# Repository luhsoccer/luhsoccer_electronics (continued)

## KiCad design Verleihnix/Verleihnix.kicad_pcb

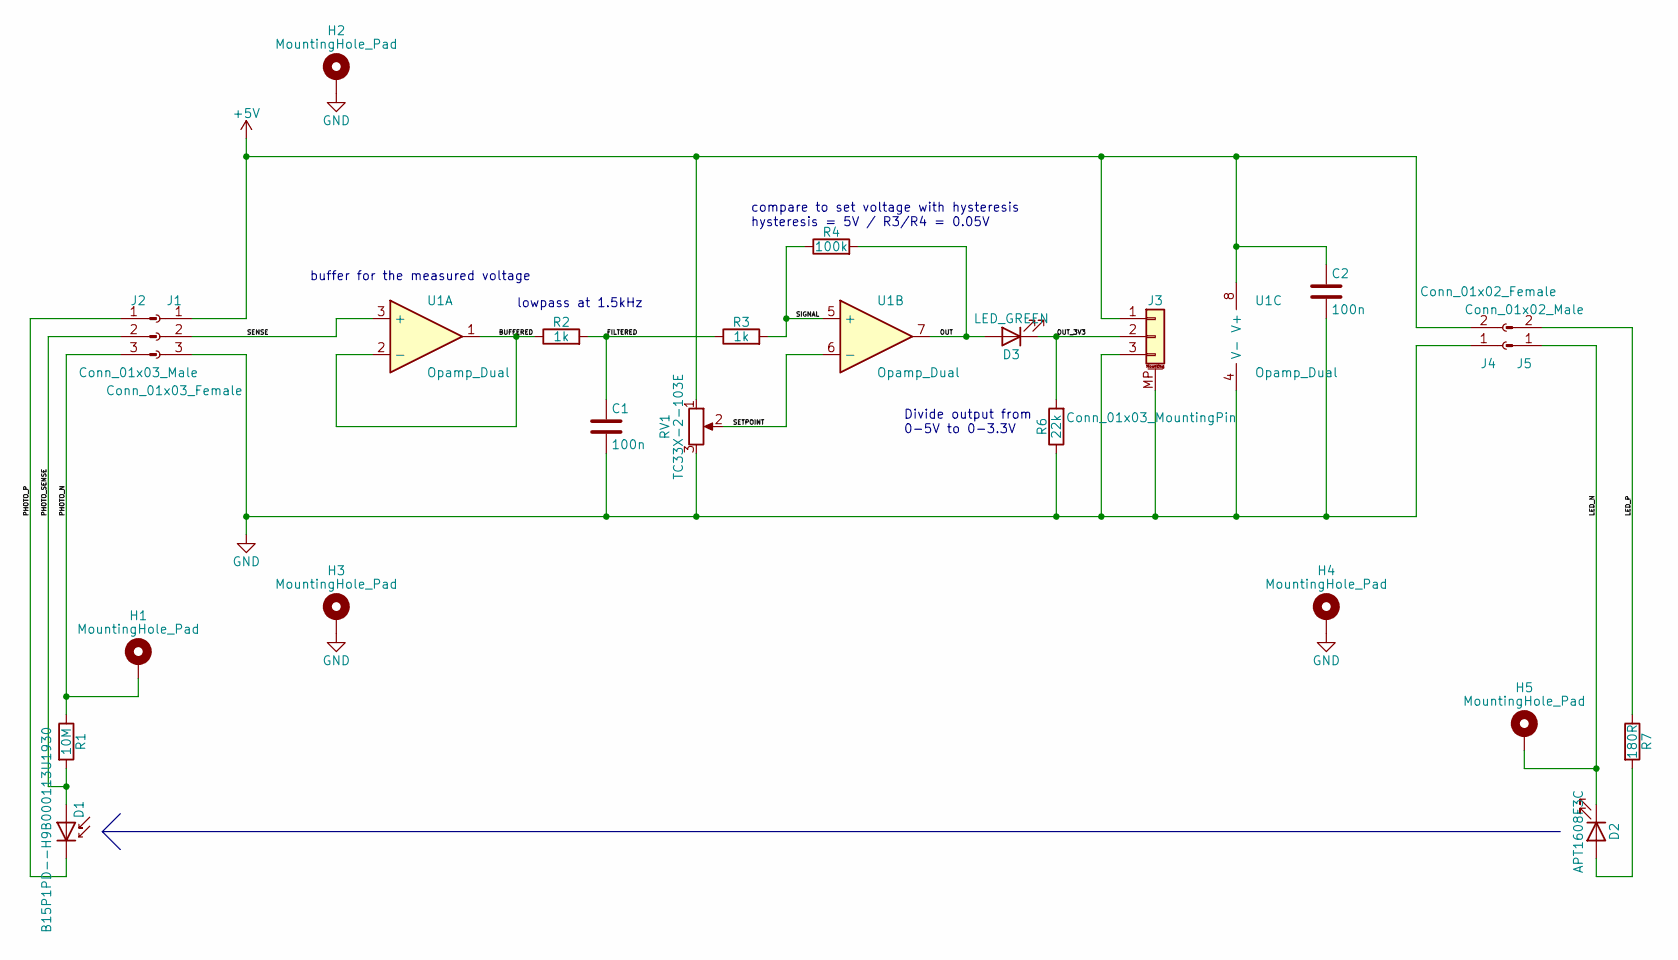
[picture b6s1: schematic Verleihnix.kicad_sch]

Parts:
C1, C2: 100n; C_0402_1005Metric
D1: B15P1PD--H9B000113U1930; LED_1210_3225Metric
D2: APT1608F3C; LED_0603_1608Metric
D3: LED_GREEN; LED_0603_1608Metric
H1, H2, H3, H4, H5: MountingHole_Pad; MountingHole_3.2mm_M3_DIN965_Pad
J1: Conn_01x03_Female; PinSocket_1x03_P2.54mm_Vertical
J2: Conn_01x03_Male; Pinheader_P2.54_01x03_Horizontal
J3: Conn_01x03_MountingPin; JST_PH_B3B-PH-SM4-TB_1x03-1MP_P2.00mm_Vertical
J4: Conn_01x02_Female; PinSocket_1x02_P2.54mm_Vertical
J5: Conn_01x02_Male; Pinheader_P2.54_01x02_Horizontal
R1: 10M; R_0402_1005Metric
R2, R3: 1k; R_0402_1005Metric
R4: 100k; R_0402_1005Metric
R6: 22k; R_0402_1005Metric
R7: 180R; R_0603_1608Metric
RV1: TC33X-2-103E; Potentiometer_Bourns_TC33X_Vertical
U1: Opamp_Dual; SOIC-8_3.9x4.9mm_P1.27mm

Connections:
+5V: C2.1, J1.1, J3.1, J4.2, RV1.1, U1.8 (V+)
/BUFFERED: R2.1, U1.1, U1.2 (-)
/FILTERED: C1.1, R2.2, R3.1
/LED_N: D2.1 (K), H5.1, J5.1
/LED_P: J5.2, R7.1
/OUT: D3.2 (A), R4.2, U1.7
/OUT_3V3: D3.1 (K), J3.2, R6.2
/PHOTO_N: H1.1, J2.3, R1.1
/PHOTO_P: D1.1 (K), J2.1
/PHOTO_SENSE: D1.2 (A), J2.2, R1.2
/SENSE: J1.2, U1.3 (+)
/SETPOINT: RV1.2, U1.6 (-)
/SIGNAL: R3.2, R4.1, U1.5 (+)
GND: C1.2, C2.2, H2.1, H3.1, H4.1, J1.3, J3.3, J3.MP (MountPin), J4.1, R6.1, RV1.3, U1.4 (V-)
unnamed: D2.2 (A), R7.2

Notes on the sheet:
compare to set voltage with hysteresis hysteresis = 5V / R3/R4 = 0.05V
buffer for the measured voltage
Divide output from 0-5V to 0-3.3V
lowpass at 1.5kHz

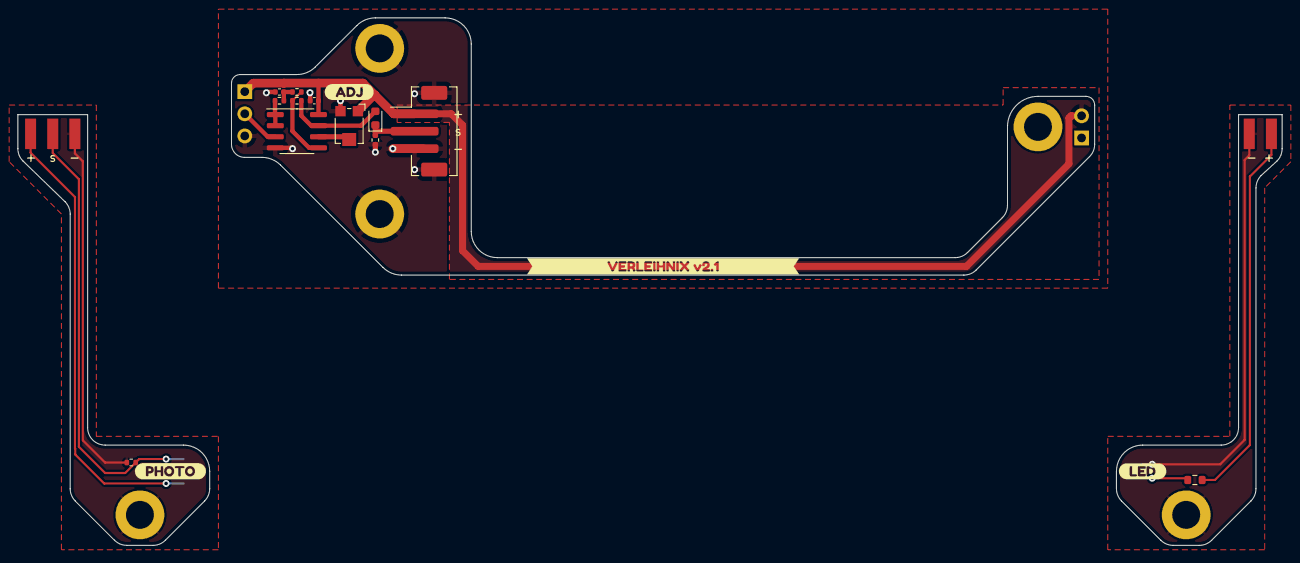
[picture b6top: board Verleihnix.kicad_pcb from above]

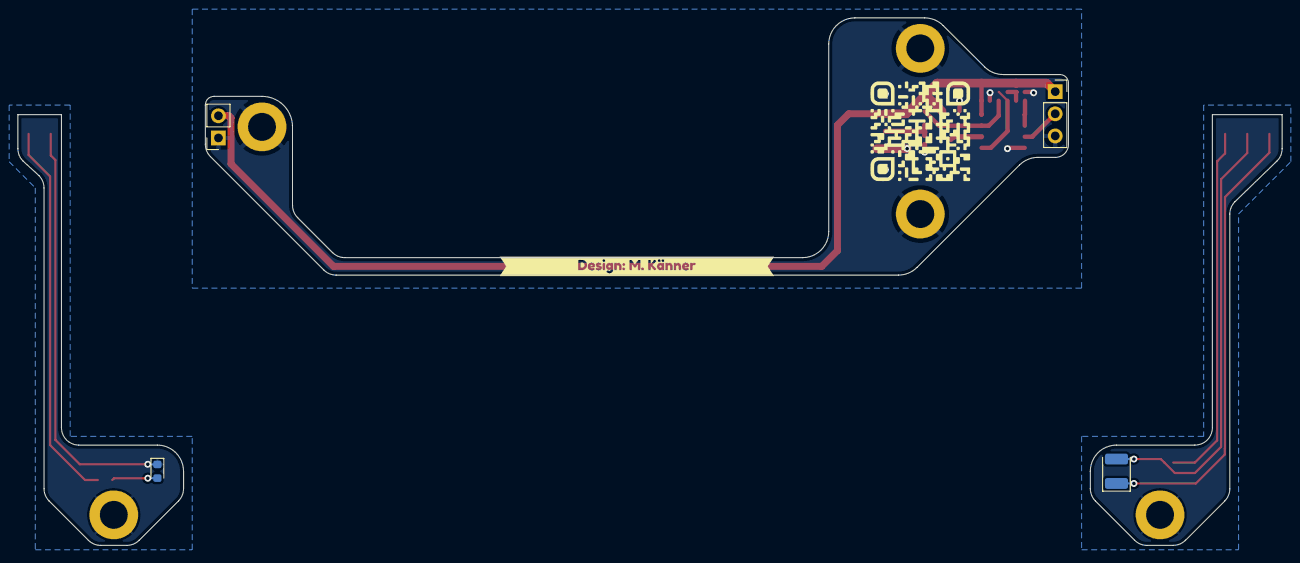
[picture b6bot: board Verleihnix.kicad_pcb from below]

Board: 2 copper layers, 145.0 x 60.5 mm, 28 parts (5 on the bottom side), 15 nets.

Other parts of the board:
kibuzzard-63F3637C: G***; kibuzzard-63F3637C
kibuzzard-635AD9F8: G***; kibuzzard-635AD9F8
kibuzzard-635AD93F: G***; kibuzzard-635AD93F
kibuzzard-635AD94A: G***; kibuzzard-635AD94A
kibuzzard-635AE38B: G***; kibuzzard-635AE38B

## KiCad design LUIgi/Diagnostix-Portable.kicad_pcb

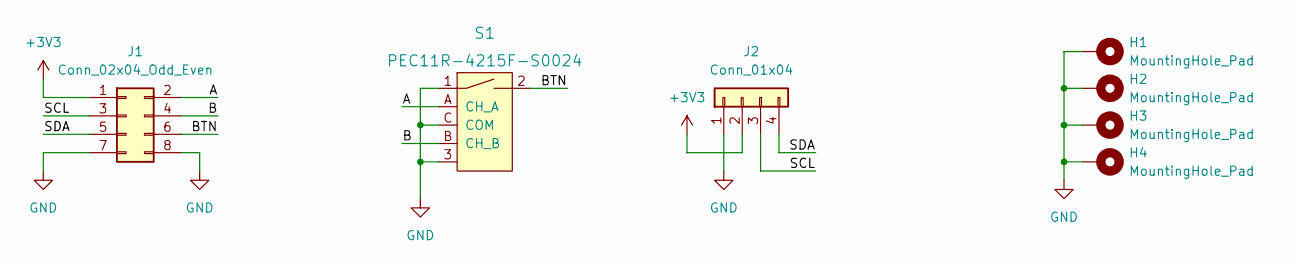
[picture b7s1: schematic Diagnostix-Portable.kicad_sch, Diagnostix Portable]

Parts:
H1, H2, H3, H4: MountingHole_Pad; MountingHole_3.2mm_M3_DIN965_Pad
J1: Conn_02x04_Odd_Even; IDC-Header_2x04_P2.54mm_Vertical
J2: Conn_01x04; PinSocket_1x04_P2.54mm_Vertical
S1: PEC11R-4215F-S0024; Rotary_Encoder_Switched_PEC11R; MPN PEC11R-4215F-S0024; Digi-Key_PN PEC11R-4215F-S0024-ND

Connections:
+3V3: J1.1, J2.2
/A: J1.2, S1.A (CH_A)
/B: J1.4, S1.B (CH_B)
/BTN: J1.6, S1.2
/SCL: J1.3, J2.3
/SDA: J1.5, J2.4
GND: H1.1, H2.1, H3.1, H4.1, J1.7, J1.8, J2.1, S1.1, S1.3, S1.C (COM)

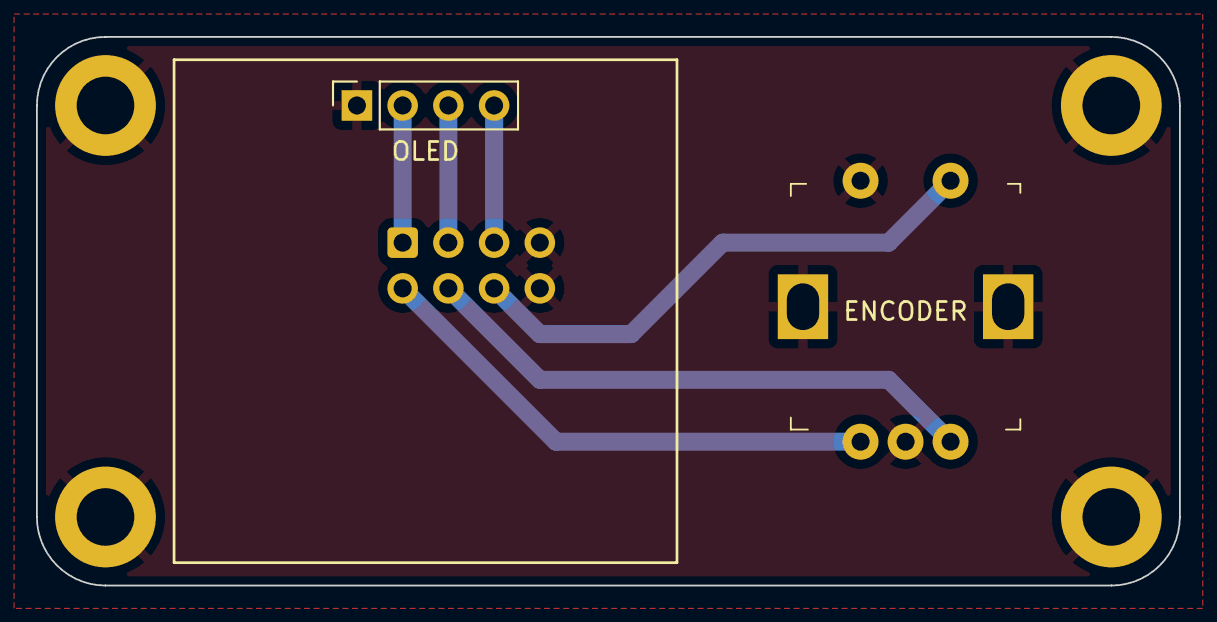
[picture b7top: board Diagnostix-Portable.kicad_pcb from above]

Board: 2 copper layers, 63.5 x 30.5 mm, 7 parts (1 on the bottom side), 7 nets.

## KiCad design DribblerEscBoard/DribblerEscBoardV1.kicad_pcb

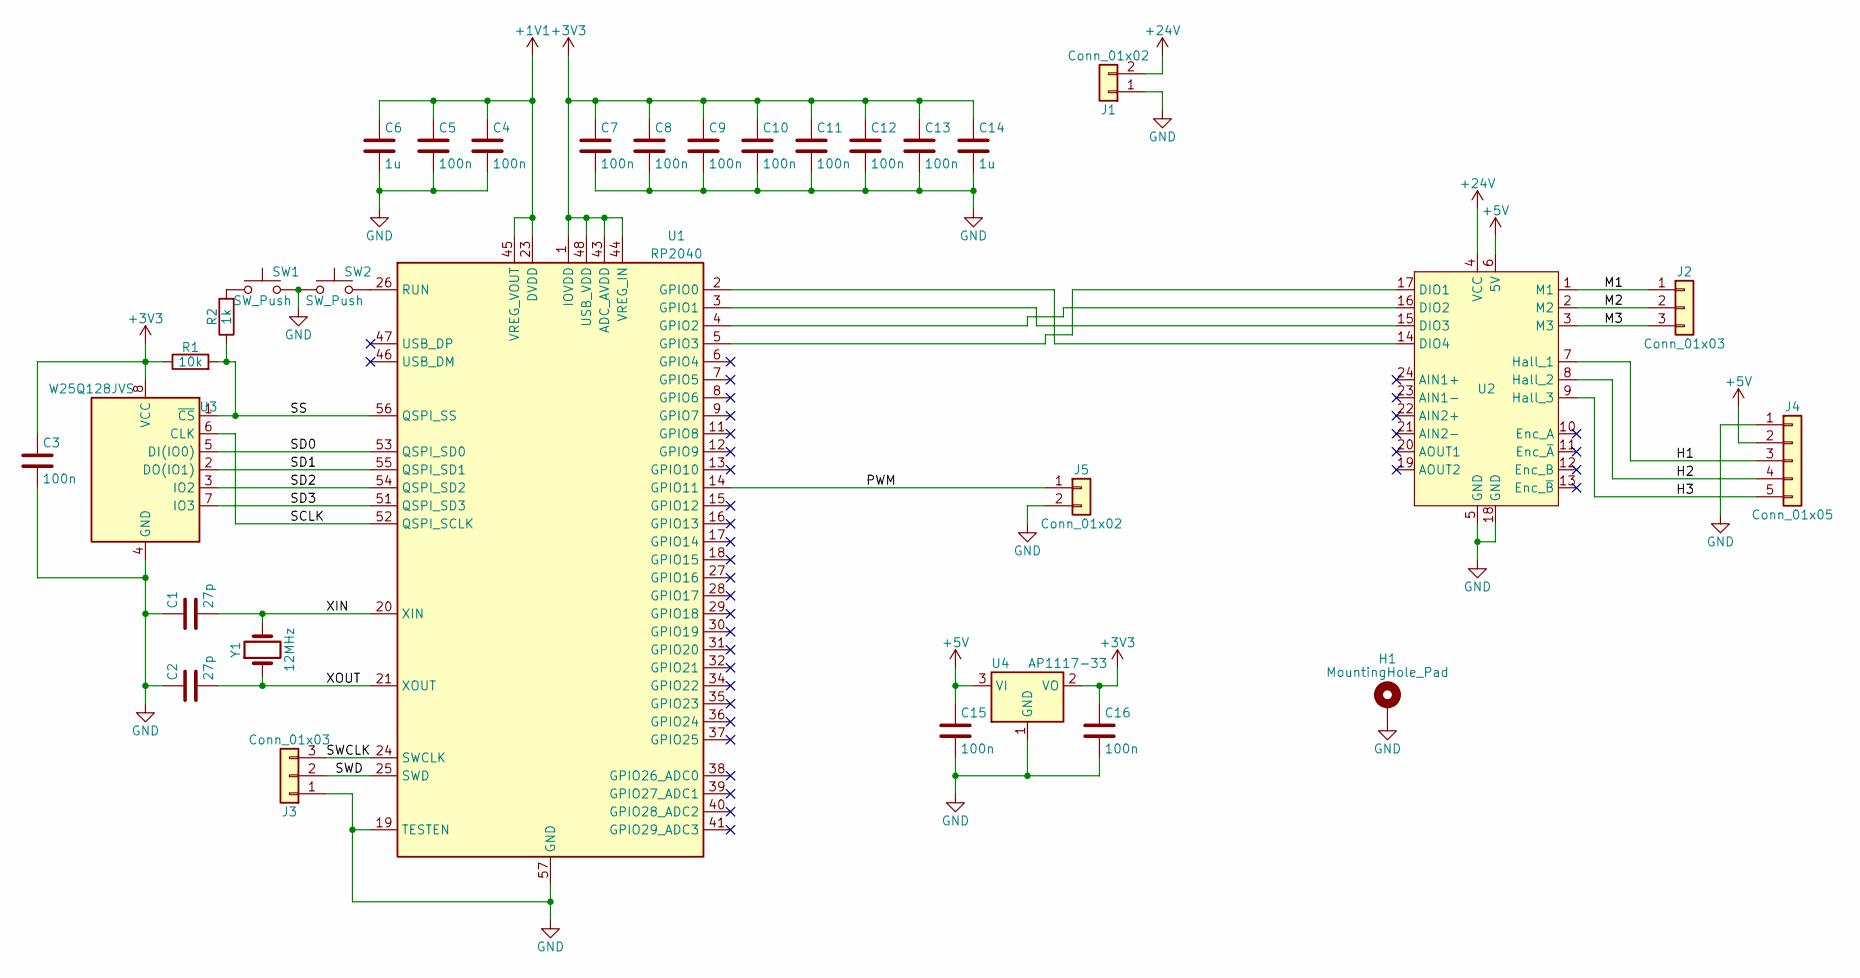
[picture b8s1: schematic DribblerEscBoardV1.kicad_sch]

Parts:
C1, C2: 27p; C_0402_1005Metric
C3, C4, C5, C7, C8, C9, C10, C11, C12, C13, C15, C16: 100n; C_0402_1005Metric
C6, C14: 1u; C_0402_1005Metric
H1: MountingHole_Pad; MountingHole_3.2mm_M3_DIN965_Pad
J1: Conn_01x02; Molex_Micro-Fit_3.0_43650-0215_1x02_P3.00mm_Vertical
J2: Conn_01x03; Molex_Micro-Fit_3.0_43650-0315_1x03_P3.00mm_Vertical
J3: Conn_01x03; PinHeader_1x03_P2.54mm_Vertical
J4: Conn_01x05; JST_PH_B5B-PH-K_1x05_P2.00mm_Vertical
J5: Conn_01x02; JST_PH_B2B-PH-K_1x02_P2.00mm_Vertical
R1: 10k; R_0402_1005Metric
R2: 1k; R_0402_1005Metric
SW1, SW2: SW_Push; SolderJumper-2_P1.3mm_Open_RoundedPad1.0x1.5mm
U1: RP2040; QFN-56-1EP_7x7mm_P0.4mm_EP3.2x3.2mm
U2: ESCON-Module-24-2
U3: W25Q128JVS; SOIC-8_5.23x5.23mm_P1.27mm
U4: AP1117-33; SOT-23
Y1: 12MHz; Crystal_SMD_5032-2Pin_5.0x3.2mm

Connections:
+1V1: C4.1, C5.1, C6.1, U1.23 (DVDD), U1.45 (VREG_VOUT), U1.50 (DVDD)
+3V3: C3.1, C7.1, C8.1, C9.1, C10.1, C11.1, C12.1, C13.1, C14.1, C16.1, R1.1, U1.1 (IOVDD), U1.10 (IOVDD), U1.22 (IOVDD), U1.33 (IOVDD), U1.42 (IOVDD), U1.43 (ADC_AVDD), U1.44 (VREG_IN), U1.48 (USB_VDD), U1.49 (IOVDD), U3.8 (VCC), U4.2 (VO)
+5V: C15.1, J4.2, U2.6 (5V), U4.3 (VI)
+24V: J1.2, U2.4 (VCC)
/H1: J4.3, U2.7 (Hall_1)
/H2: J4.4, U2.8 (Hall_2)
/H3: J4.5, U2.9 (Hall_3)
/M1: J2.1, U2.1 (M1)
/M2: J2.2, U2.2 (M2)
/M3: J2.3, U2.3 (M3)
/PWM: J5.1, U1.14 (GPIO11)
/SCLK: U1.52 (QSPI_SCLK), U3.6 (CLK)
/SD0: U1.53 (QSPI_SD0), U3.5 (DI(IO0))
/SD1: U1.55 (QSPI_SD1), U3.2 (DO(IO1))
/SD2: U1.54 (QSPI_SD2), U3.3 (IO2)
/SD3: U1.51 (QSPI_SD3), U3.7 (IO3)
/SS: R1.2, R2.1, U1.56 (QSPI_SS), U3.1 (~CS)
/SWCLK: J3.3, U1.24 (SWCLK)
/SWD: J3.2, U1.25 (SWD)
/XIN: C1.2, U1.20 (XIN), Y1.2
/XOUT: C2.2, U1.21 (XOUT), Y1.1
GND: C1.1, C2.1, C3.2, C4.2, C5.2, C6.2, C7.2, C8.2, C9.2, C10.2, C11.2, C12.2, C13.2, C14.2, C15.2, C16.2, H1.1, J1.1, J3.1, J4.1, J5.2, SW1.2, SW2.1, U1.19 (TESTEN), U1.57 (GND), U2.5 (GND), U2.18 (GND), U3.4 (GND), U4.1 (GND)
unnamed: R2.2, SW1.1
unnamed: U1.2 (GPIO0), U2.14 (DIO4)
unnamed: U1.3 (GPIO1), U2.15 (DIO3)
unnamed: U1.4 (GPIO2), U2.16 (DIO2)
unnamed: U1.5 (GPIO3), U2.17 (DIO1)
unnamed: SW2.2, U1.26 (RUN)

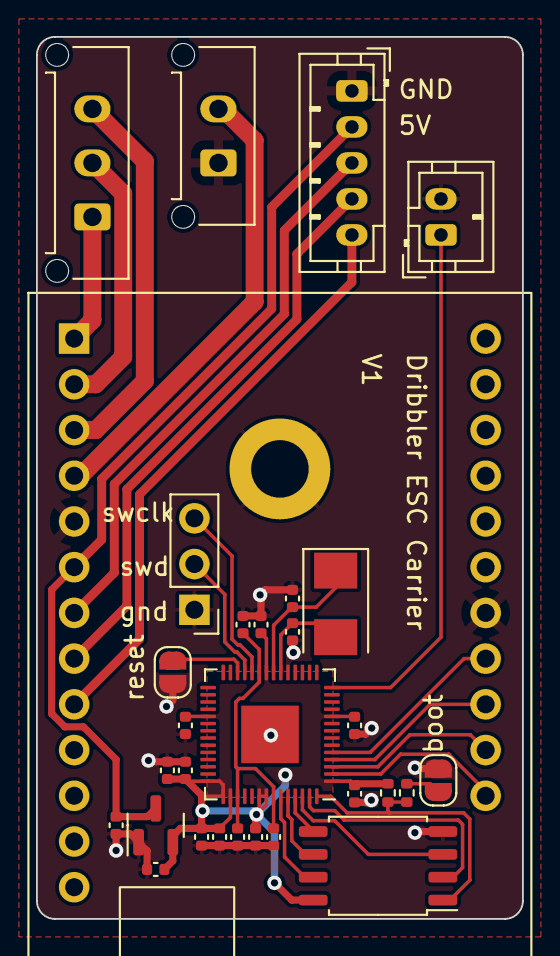
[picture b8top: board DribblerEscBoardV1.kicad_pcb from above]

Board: 2 copper layers, 27.0 x 49.0 mm, 31 parts (0 on the bottom side), 28 nets.

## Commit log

2023-07-03 luhbots Soccer Open Source Release 2023
